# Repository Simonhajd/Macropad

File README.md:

the LRP:
Mice are clunky for photo editing - you have to look at the cursor to edit photos, while trying to look at the changes on the photo at the same time!
Introducing: LRP: an Adobe Lightroom tool to remove the mouse from photo editing.

features a key to move to the next editing option, and a potentiometer to physically change the image settings on-screen

CAD Model:

PCB (Made in KICAD):

Case Design:

Cool knob i made for the rotary encoder:

BOM:

1x Cherry MX Switches

1x DSA Keycaps

1x SK6812 MINI-E LEDs

1x 0.91" 128x32 OLED Display

1x EC11 Rotary Encoder

1x XIAO RP2040

1x Case (3 printed parts) 

4x M3x16mm screws

4x M3x5mx4mm heatset inserts

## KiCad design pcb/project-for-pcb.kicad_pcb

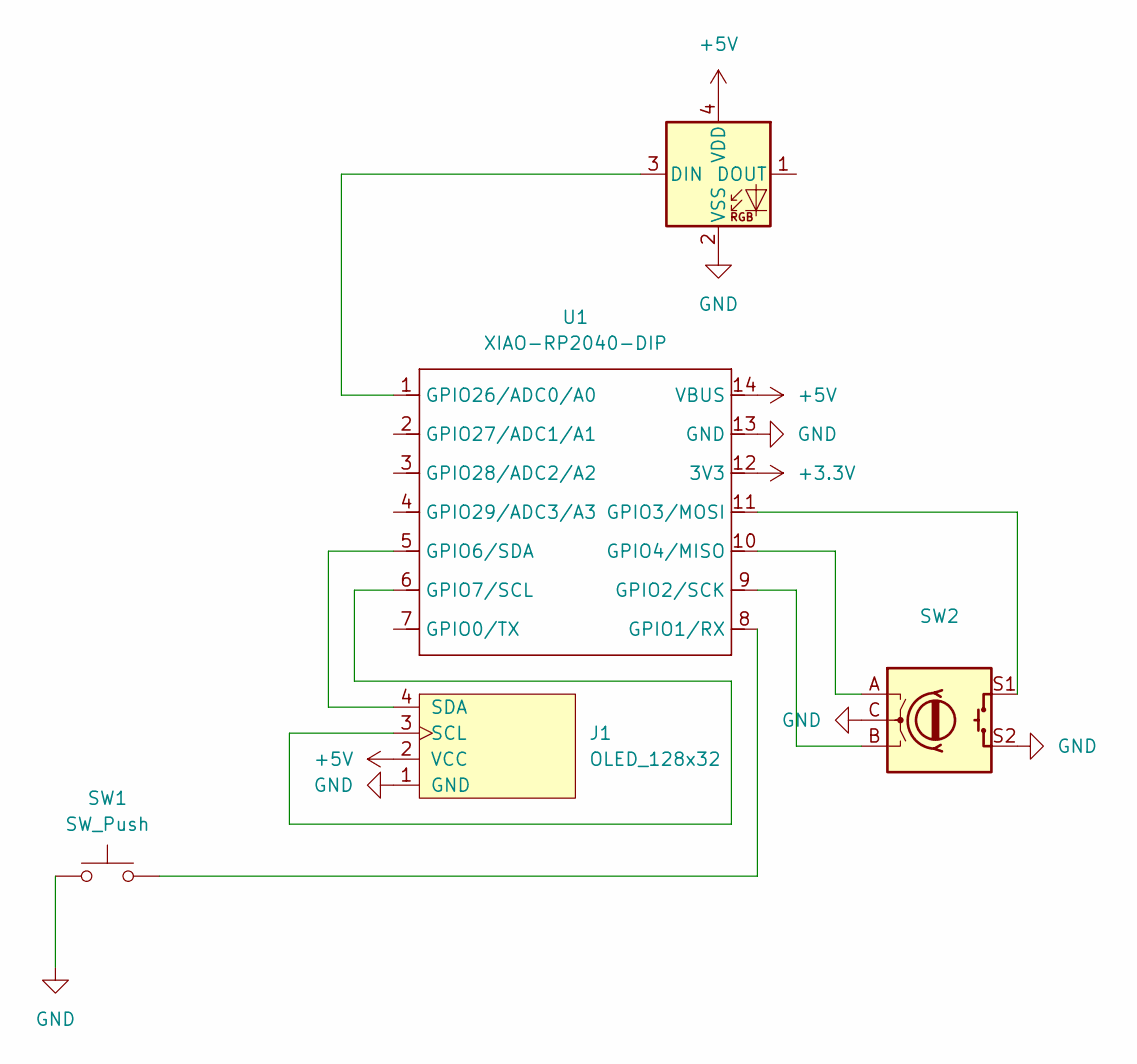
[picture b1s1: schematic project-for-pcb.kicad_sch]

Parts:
D1: SK6812MINI; LED_SK6812MINI_PLCC4_3.5x3.5mm_P1.75mm
J1: OLED_128x32
SW1: SW_Push; SW_Cherry_MX_1.00u_PCB
SW2: RotaryEncoder_Switch; RotaryEncoder_Alps_EC11E-Switch_Vertical_H20mm
U1: XIAO-RP2040-DIP

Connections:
+3.3V: U1.12 (3V3)
+5V: D1.4 (VDD), J1.2 (VCC), U1.14 (VBUS)
GND: D1.2 (VSS), J1.1 (GND), SW1.1, SW2.C, SW2.S2, U1.13 (GND)
unnamed: D1.3 (DIN), U1.1 (GPIO26/ADC0/A0)
unnamed: J1.3 (SCL), U1.6 (GPIO7/SCL)
unnamed: J1.4 (SDA), U1.5 (GPIO6/SDA)
unnamed: SW1.2, U1.8 (GPIO1/RX)
unnamed: SW2.B, U1.9 (GPIO2/SCK)
unnamed: SW2.S1, U1.11 (GPIO3/MOSI)
unnamed: SW2.A, U1.10 (GPIO4/MISO)

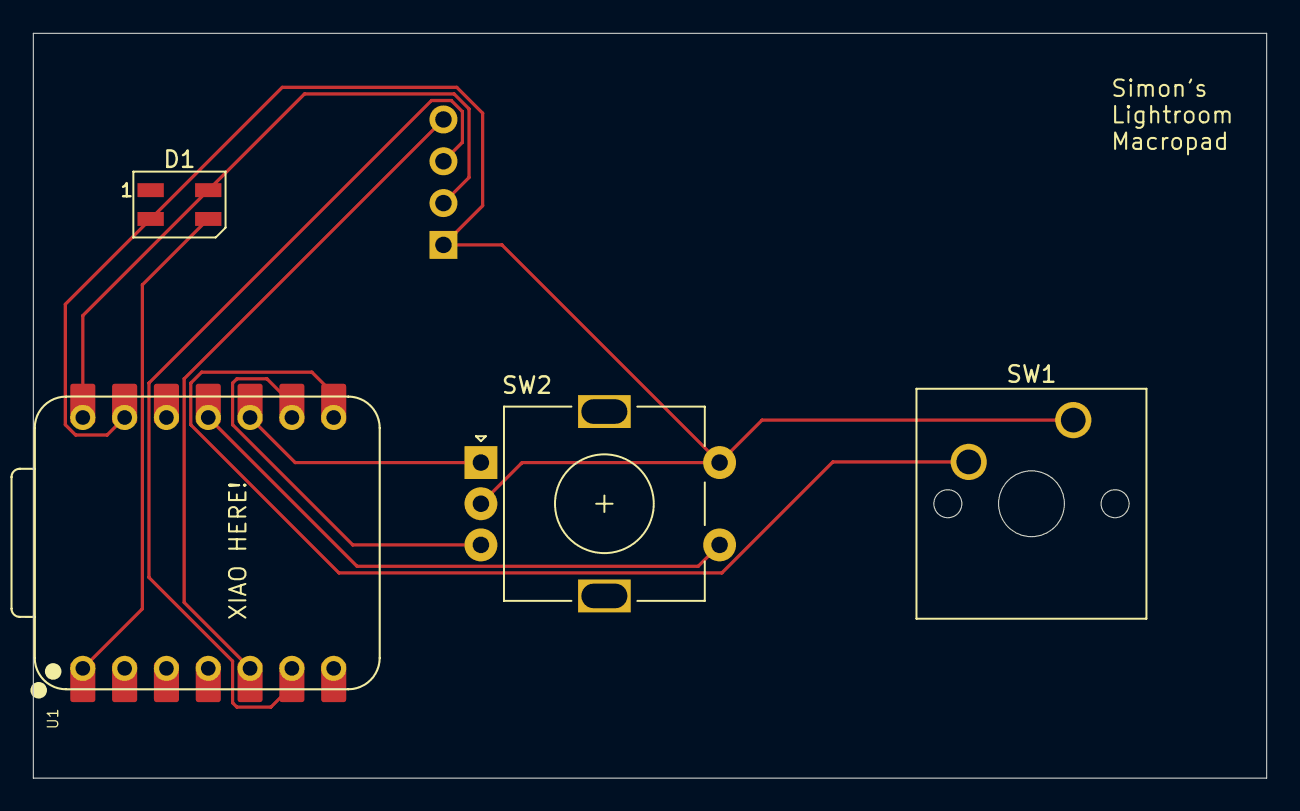
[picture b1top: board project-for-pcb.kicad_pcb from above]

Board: 2 copper layers, 74.9 x 45.2 mm, 5 parts (0 on the bottom side), 9 nets.

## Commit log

2025-05-26 all the files!
2025-05-26 more files!
2025-06-10 PCB changes
    lot of changes to the pcb - made it much smaller. case is way overengineered now and i need to add an on/off, and a mechanicm for the mudule to latch to the main case.
